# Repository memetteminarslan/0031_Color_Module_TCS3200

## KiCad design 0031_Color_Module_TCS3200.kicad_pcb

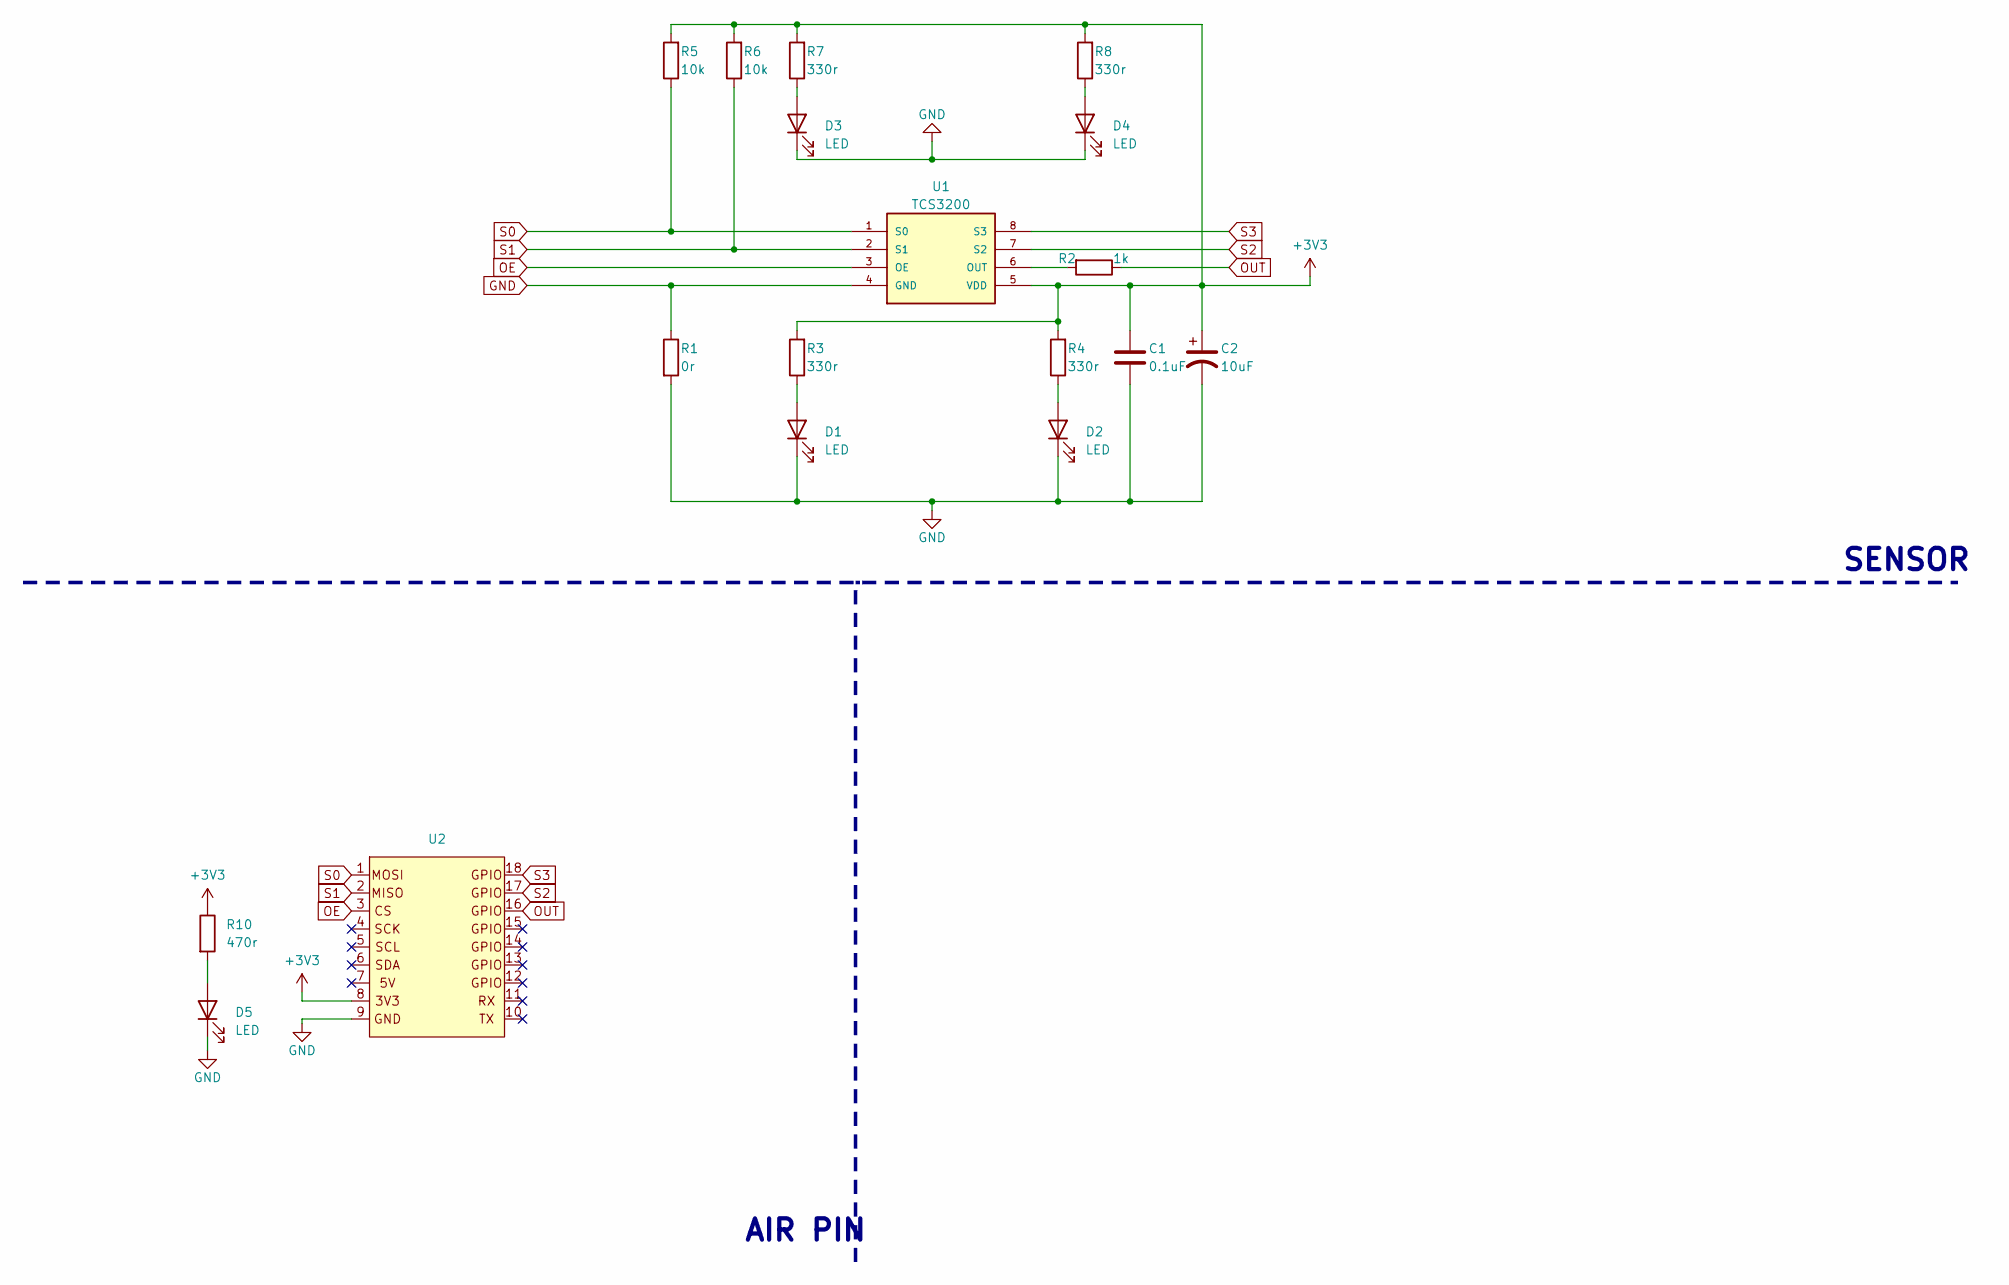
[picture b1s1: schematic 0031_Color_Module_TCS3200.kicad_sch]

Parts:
C1: 0.1uF; C_0805_2012Metric
C2: 10uF; C_1206_3216Metric
D1, D2, D3, D4: LED; LED_D3.0mm
D5: LED; LED_0805_2012Metric
R1: 0r; R_0805_2012Metric
R2: 1k; R_0805_2012Metric
R3, R4, R7, R8: 330r; R_0805_2012Metric
R5, R6: 10k; R_0805_2012Metric
R10: 470r; R_0805_2012Metric
U1: TCS3200; SOIC8
U2: pin_header

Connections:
+3V3: C1.1, C2.1, R3.2, R4.2, R5.2, R6.2, R7.2, R8.2, R10.1, U1.5 (VDD), U2.8
GND: C1.2, C2.2, D1.1 (K), D2.1 (K), D3.1 (K), D4.1 (K), D5.1 (K), R1.1, R1.2, U1.4 (GND), U2.9
unnamed: D1.2 (A), R3.1
unnamed: D2.2 (A), R4.1
unnamed: D3.2 (A), R7.1
unnamed: D4.2 (A), R8.1
unnamed: D5.2 (A), R10.2
unnamed: R2.2, U1.6 (OUT)
OE: U1.3 (OE), U2.3
OUT: R2.1, U2.16
S0: R5.1, U1.1 (S0), U2.1
S1: R6.1, U1.2 (S1), U2.2
S2: U1.7 (S2), U2.17
S3: U1.8 (S3), U2.18

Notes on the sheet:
AIR PIN
SENSOR

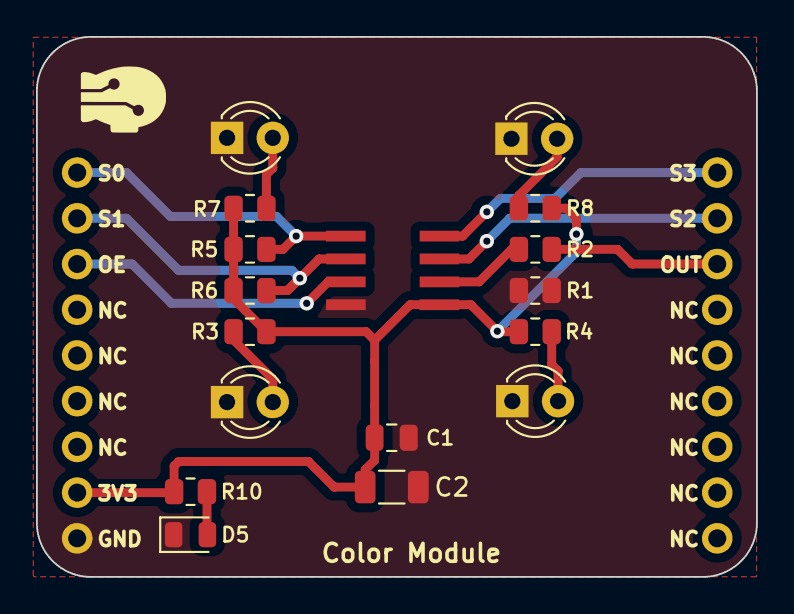
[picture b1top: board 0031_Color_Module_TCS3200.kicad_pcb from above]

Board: 2 copper layers, 40.0 x 30.0 mm, 18 parts (0 on the bottom side), 14 nets.
